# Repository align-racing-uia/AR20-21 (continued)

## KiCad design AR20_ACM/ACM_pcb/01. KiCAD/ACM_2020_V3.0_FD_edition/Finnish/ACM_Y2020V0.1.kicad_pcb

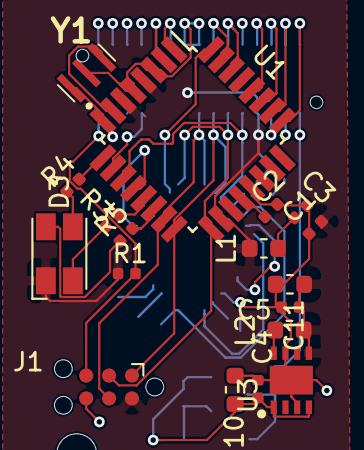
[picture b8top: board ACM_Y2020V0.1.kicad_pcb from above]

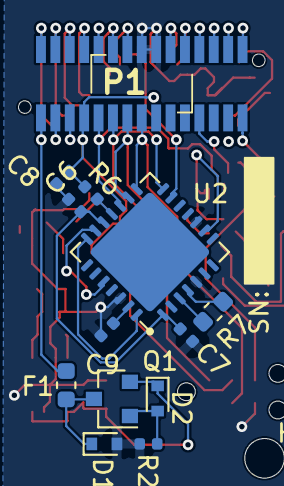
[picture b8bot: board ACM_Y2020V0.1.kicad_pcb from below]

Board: 2 copper layers, 32 parts (14 on the bottom side), 40 nets.

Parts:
C1, C2, C3, C4, C5, C6, C7, C8, C9: 0.1uF; C_0402_1005Metric
C10, C11: 10uF; C_0603_1608Metric
D1: 15V; D_SOD-523
D2: 2.4V; D_SOD-523
D3: ASMB-MTB0-0A3A2; LED_Avago_PLCC4_3.2x2.8mm_CW
F1: 250mA; Fuse_0603_1608Metric
H1: M2 Mouting hole; MountingHole_2.2mm_M2
J1: TC2030-MCP-NL; Tag-Connect_TC2030-IDC-NL_2x03_P1.27mm_Vertical
L1: 10uH; L_0603_1608Metric
L2: 2.2 µH; L_0603_1608Metric
P1: Conn_02x15_Odd_Even; ILWX10SBVFBE
Q1: Q_PMOS_DGS; SOT-23
R1, R6: 10K Ohm; R_0402_1005Metric
R2: 100K Ohm; R_0402_1005Metric
R3: 290 ohm; R_0402_1005Metric
R4: 200ohm; R_0402_1005Metric
R5: 190 Ohm; R_0402_1005Metric
R7: 120 Ohm; R_0603_1608Metric
U1: ATmega328P-AU; TQFP-32_7x7mm_P0.8mm
U2: MCP25625-x-SS; QFN-28-1EP_6x6mm_P0.65mm_EP4.8x4.8mm
U3: NCV890430MW50TXG; SON65P300X300X100-9N
Y1: 16.0Mhz; CSTNE16M0V530000R0

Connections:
+5V: C1.1, C5.1, C6.1, C11.1, D3.1, J1.2, L1.1, L2.2, P1.7, R1.1, R6.2, U1.4, U1.6, U1.18, U3.5
+12V: F1.2, P1.1
+12V_Safe: C4.1, C10.1, D2.1, Q1.2, U3.1, U3.4
/BLUE_LED: R5.2, U1.14
/CAN_CS: P1.9, U1.11, U2.17
/CAN_INT: U1.32, U2.13
/CLK_MCP: U1.12, U2.9
/GREEN_LED: R4.2, U1.9
/MISO: J1.1, P1.13, U1.16, U2.16
/MOSI: J1.4, P1.15, U1.15, U2.15
/RED_LED: R3.2, U1.13
/Reset: J1.5, P1.29, R1.2
/SCK: J1.3, P1.11, U1.17, U2.14
/U-Pin1: R7.2, U2.3
/U-Pin2: P1.2, U1.25
/U-Pin3: R7.1, U2.4
/U-Pin4: P1.4, U1.26
/U-Pin6: P1.6, U1.27
/U-Pin8: P1.8, U1.28
/U-Pin12: P1.12, U1.30
/U-Pin14: P1.14, U1.31
/U-Pin20: P1.20, U1.1
/U-Pin22: P1.22, U1.2
/U-Pin23: P1.23, U1.10
GND: C1.2, C2.2, C3.1, C4.2, C5.2, C6.2, C7.2, C8.2, C9.1, C10.2, C11.2, D1.2, J1.6, P1.16, P1.18, R2.2, U1.3, U1.5, U1.21, U2.5, U2.10, U2.26, U3.3, U3.7, U3.9, Y1.2
unnamed: C2.1, U1.20
unnamed: C3.2, L1.2
unnamed: C7.1, C8.1, U2.1, U2.19
unnamed: C9.2, U2.27
unnamed: D1.1, F1.1, Q1.3
unnamed: D2.2, Q1.1, R2.1
unnamed: D3.2, R5.1
unnamed: D3.3, R4.1
unnamed: D3.4, R3.1
unnamed: L2.1, U3.8
unnamed: R6.1, U2.18
unnamed: U1.7, Y1.3
unnamed: U1.8, Y1.1
unnamed: U2.20, U2.24
unnamed: U2.21, U2.28

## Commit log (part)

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2019-11-11 Fixed test points
2019-11-11 MCP25625 Breakoutboard Ready
2019-11-11 Added Gerberfiles
2019-11-13 CPU canEvents
2019-11-13 Breakout Cpu
    WIP
2019-11-14 Breakout CPU FIX
    fixed can
2019-11-14 Breakout CPU no connections added
2019-11-14 Breakout CPU with SD card
2019-11-14 CPU RTOS Msgs added
    Can send strings between threads
2019-11-18 Uart brakeout board
2019-11-20 Auto stash amerge of "master" and "origin/master"
2019-11-20 CPU Stash
2019-11-20 Flyttet på komponent
2019-11-20 Auto stash before merge of "master" and "origin/master"
2019-11-20 mohammad_edition
2019-11-20 Created Simon Edition Folder
2019-11-20 AtmegaFix
2019-11-20 Exploded and connected MCP25625 RX and TX
2019-11-20 Exploded and connected MCP25625 RX and TX 2
2019-11-20 Edited schematic breakout teensy
2019-11-20 Added right ICSP connector pinout
2019-11-20 Revert "Merge branch 'master' into GPS"
    This reverts commit eede9093351da36afd50b96e1e304890f671bac6.
2019-11-22 Added footprint to connectors
2019-11-22 Edited test points
2019-11-22 ADDED NEW FOOTPRINT TO TEENSY CONNECTORS
2019-11-22 FOOTPRINT IS DONE
2019-11-24 Added some trace to PCB
2019-11-24 initial traces is done
2019-11-24 Made a copy of Teensy schematic
2019-11-27 Edited library
2019-11-29 Edited the layout
2019-12-04 Edited to 4 layers
2019-12-06 4 Layers PCB is 90% finished
2019-12-09 BreakoutBoard final edit
2019-12-10 Edited the Vreg to SD
2019-12-18 Edited
2020-01-07 Created Steering Angle sensor PCB
2020-01-07 Added: 90deg JST XH connector
2020-01-07 Added Renders
2020-01-07 Changed size due to 10x10mm potmeter
2020-01-07 Updated Render
2020-01-11 Added: M. Edition
2020-01-12 ready pcb ACM
2020-01-12 ACM Folder Cleanup
2020-01-12 Fixed push button
2020-01-12 ACM-pcb full connected
    ACM -12.01
2020-01-12 final one 12.01
2020-01-12 Ronded corner and added a angle
2020-01-12 Set PCB Size and started on ACM footprint
2020-01-12 Added GND to Pin 9 and checked connector output
2020-01-12 Created ACM2020 Footprint (.kicad_mod) and Symbol (.lib)
2020-01-13 Created ACM Breakout
2020-01-13 Pad to close to pad issue
2020-01-13 Pad to close to pad
2020-01-13 Generated Gerber
2020-01-13 GerberFile Generated
2020-01-13 Generated Breakout Gerber
2020-01-13 Generated ACM Gerber
2020-01-14 Gerber
2020-01-15 Added Telemetry Extention folder
2020-01-15 Added ACM Library: See Git description
    Added ACM footprint
    Added ACM Symbol
2020-01-17 Intitialized ACM Pedalbox
2020-01-17 Created PlatformIO Project
2020-01-17 Created converted emulator
2020-01-18 Checkout
2020-01-18 Checkout ()
2020-01-18 Added symbols
2020-01-19 Git ignore
2020-01-20 Created ETBC Ramp function
2020-01-20 Testet ETBC with ramp functions and oscilloscope.
2020-01-20 Added math in Waveforms
2020-01-21 NEW Gerber File generated
2020-01-21 Gerber.zip
2020-01-22 Added data from the car
2020-01-22 Added lots of stuff
2020-01-22 Closed waveforms
2020-01-22 Added ACM2020 Footprint
2020-01-22 Initialized: Pedalbox Extention board
2020-01-22 See Changelog
    Added: ACM Library
    Added: 2x Voltage dividers
    Added: Connector
2020-01-23 Started on PCB layout and added 18pin connector
2020-01-23 Initialized new ETBC controller
2020-01-23 Added libraries
2020-01-23 Ignore me
2020-01-23 Started on schematic
2020-01-24 Added new test data on bench for 40mm ETB.
2020-01-24 Matlab Fourier Transform Script
2020-01-27 Finnish Matlab Fourier script (See Description)
    Unsure if the X-axis is right.
2020-01-27 Shematic
    Added leds
    Added small components
2020-01-28 Connector change
2020-01-29 Pedalbox PCB Ready - Just need some more silkscreen... ;)
2020-01-30 Edit pads
2020-01-30 Edit pads and traces
2020-01-30 Fixed traces, changed ACM footprint and generated gerber
2020-01-30 Gerber file 1.0 generated
2020-01-30 Generated gerber for breakout board
2020-01-30 Generated Gerber Zip
2020-01-30 Added Endurance race
2020-01-31 Created LPF calc
2020-01-31 Added Resistor and capacitor to calc
2020-01-31 Created PCB BOM
2020-02-01 Low pass filter calc
2020-02-02 Added connector
2020-02-02 Added ACM Connector
2020-02-02 Added filters
2020-02-03 Added controller datasheet
2020-02-03 Se Changelog in description
    Changed connector
    Added Capacitors
    Set footprints
2020-02-04 Datasheet save
2020-02-04 Uknown
2020-02-07 Frequency test
2020-02-09 Voltage_Regulator added
2020-02-09 Added MCP25625 symbol
2020-02-09 Made v0.1
2020-02-10 ecuCode
2020-02-10 Connector footprint added
2020-02-10 Connector added
2020-02-11 Fourier Transform fix
2020-02-11 DataLoggerAR20
2020-02-12 Created 3D Step of Pedal MCU
2020-02-12 Frequency test (10Hz - 50Hz, 10Hz intervall)
2020-02-12 Size of PCB
2020-02-17 ETBC code
2020-02-17 Created functions.h
2020-02-17 code V1.1 testing
2020-02-18 Added different types of waveforms functions
2020-02-20 Generated EGS folder
2020-02-26 Code V1.2
2020-02-29 Alot of polishing, and bug fixes, se description.
    - Fixed wrong header names in CSV
    - Reduced decimal precision
    - Added a SD_operations file, where all SD operations occur
    - Changed data rate to 100ms
    - Added F macro to texts, to reduce ram usage. Program failed due high ram usage.
    - Added temperature sensor bound's.
2020-03-02 Created BOM
2020-03-02 Prototype board extention
2020-03-03 Value change
2020-03-03 Changed footprint
2020-03-03 ETC PCB Layout
2020-03-04 Added correct MCP25625 symbol - Need to be converted in schematic
2020-03-04 Adjusted footprints and created BOM
2020-03-04 ACM_V2.0 edition: Ny pcb design
    fixet MCP footprint
2020-03-05 ETBC Semi complete - Evryting connected. Check description
    Neec to check all footprints.
    Need to check all symbols (Pin numbering correspond to footprint and datasheet)
    Need to check JLCPCB DRC settings.
2020-03-06 ETBC Complete
2020-03-07 Simon adjustment 1 of 2
2020-03-07 Checked MCP25625 and adjusted traces.
2020-03-07 V2.0 Teensy Breakout Board
2020-03-07 Push button edited
2020-03-08 Edited traces
2020-03-09 Added Datasheets
2020-03-12 Created 3D Model
2020-03-22 Settings adjustment
2020-03-25 Endret SCLK pin til SD
2020-03-30 code settings
2020-03-31 More PWM Datapoints
2020-04-29 Generated Renders for V1.1
2020-05-11 Generated 3D Model
2020-05-11 Added: 3D Component ACM connector
2020-05-16 Added: Data from Solan test
2020-05-22 Generated 3D file
2020-09-10 Deleted everything except ACM folder in ACM-branch
    Test
2020-09-15 Cleaned the inventory, Added moccup Code
2020-09-19 Cleanup
2020-09-19 test
2020-09-19 Del test
2020-09-19 Added: "Reformatting code" (Work from AR20)
2020-09-19 Cleanup
    Only AR20_Pedalbox folder in this branch.
2020-09-19 Cleanup
    Only "AR20_steeringAngle" folder in this branch
2020-09-19 Cleanup
    Only "AR20_ETC" folder in this branch.
2020-09-20 Major Cleanup Action
2020-09-20 Major Cleanup, Own Branch For RTOS
2020-09-22 Added ACM Cad in 3d View
2020-09-22 Moved library folder /lib
2020-09-23 created test.txt
2020-09-24 Fixed system in 2layer folder, probably need some more work
2020-09-27 Circuit protecion fixed
2020-09-27 Changed RGB light
2020-09-28 Minor Library fix
2020-10-01 NOT COMPLETE V3.0 ACM
    This is the beginning of the V3.0 ACM. With added CAN FD transiver and CAN FD controller.
    To fix:
    Chagne CAN FD transciver to a SOCI version
    Place all capacitors in a good location.
    Board cleanup
2020-10-03 ACM 3.0 CAN FD implemented and made SOIC
2020-10-06 Better connections
    Gave groundplane a better route and moved some 5V
2020-10-11 Added: 2x Connectors and 2x pads.
2020-10-13 Added Zener diode between 5V and ground
2020-10-18 20Mhz resonator on CAN Conrtoller
2020-10-20 High Termal Design of ETBC, on the works
    Almost done, finishing left
2020-10-21 Changed footprint for connector
2020-10-22 Work in progress
2020-10-22 Moved mosfet out of 12V safe
    Moved the mosfet outside of the safe filtered 12V. Still placed behind the fuse, so nothing interferes before the fuse does it's job.
2020-10-24 V2.3 Better design Done
    -New PCB
    -Got rid of superfluous Diode
    -Got rid of poor choise Resistors in low pass filter
2020-10-24 Some 3D Work
2020-11-02 Added namings to the ports
2020-11-07 Started creation of RS485 board
2020-11-09 Reverse polarity protection
2020-11-11 Start of V3 STM32
    Imported symbols/footprints ...
2020-11-12 Silkscreen update
2020-12-05 slight schematics cleanup
2020-12-09 Changed Zener Diode from 3.6V to 5.1V
2020-12-13 Added connector footprint to KiCad
2020-12-13 Added Protection circuit as in CAN FD ACM
2020-12-13 Deletet redundant stuff
    - deleted breakout boards, they are in the ACM brach
2020-12-13 Generated Gerber FIles
2020-12-13 Cleanup of old ACM 2.0 files And generated Gerber
    - Deleted ACM 2 First Edition. it is in ACM2.0 branch
    - Deletetd ACM 2 CAN2.0 related folders it is in ACM2.0 branch
    - Deleted Eale Project as it exist in ACM 2.0 Branch
2020-12-13 Battery PCB completed
2020-12-13 Fixed: Mounting holes
2020-12-13 Added awesome, and Generated ZiP
2020-12-13 Added awesome, and Generated Gerber
2020-12-13 Updated Silk_scr and Generated Gerber
2020-12-13 Fixed a little issue, New gerber files
2020-12-16 Footprint and schematics H7
2020-12-16 Test2
2020-12-17 Imported FDCAN Chip
2020-12-17 Added FCCAN ship from standard lib
    Regner med at denne er riktig? Har ikke sjekket om det er riktig pakning eller mål, men dette er litt forvirrende. Får ta dette med Christian
2020-12-17 Suspension disp senson schematic done
2020-12-19 Added footprints diodes ++
2020-12-30 Nearly completed schematics. Ready for tracing?
    Short cleanup in footprint library
2021-01-05 PCB trace 1.0V
    Har ikke lagt til spenningsforsyning til sensorene eller GND. Dessuten har jeg satt connectoren feil vei
2021-01-06 Schematic DONE, started tracing
2021-01-10 Trace V1.0 take 1
2021-01-10 Small fixes. Not done yet
2021-01-11 A slight Adjustment
2021-01-11 Re save
2021-01-17 Generated gerbers
2021-02-13 Created iBOM
2021-02-13 Set filtering values
2021-02-13 Updated iBOM
2021-03-03 Moved Gerber to folder and zipped it.
2021-03-13 Beginnings Gear Sensor
    The simple beginnings of a project that might revolutionize the world
2021-03-15 Added 10k resistor between VDD and CS
    As requested by the ACAN library I added a 10k resistor between VDD and CS
2021-03-15 Some demo code for gear sensor and clutch pressure
2021-03-18 Updated 10k resistor position and version
2021-03-20 V3 EGS code library based
2021-03-20 Comment
2021-03-24 Lagt til kode for testing av CANbus
2021-03-27 CANbus endringer
2021-04-07 Bug fix attempt
2021-04-07 Fungerende platformoi.ini fil som flasher kode
2021-04-11 CANbus, fungerer nesten
2021-04-11 Beginning working code for clutch servo
2021-04-12 Moved code to object oriented
2021-04-14 Dysfunctional code
2021-04-14 Compiling code
2021-04-14 Fungerer greit nok
2021-04-18 it's alive(ish)
    koden er ikke laget, men det kompilerer
2021-04-19 Startet på logikk
    Naboen går med boblejakke og spiser is
2021-04-20 Lagd mockup
    grov
2021-04-21 Mockup Code
2021-04-22 Code managed by main.cpp
2021-04-23 Code environment cleanup
2021-04-23 Hope this works
    vil ha is
2021-04-23 Commiting from VSCode
2021-04-23 Unfinnished merge between EGS and EGS logic
2021-04-23 Merge branch 'EGS_main_logic' functioning merge with logic
    Conflicts:
    AR20_EGS/EGS code V3/.pio/build/project.checksum
    AR20_EGS/EGS code V3/.vscode/c_cpp_properties.json
    AR20_EGS/EGS code V3/.vscode/extensions.json
    AR20_EGS/EGS code V3/.vscode/launch.json
    AR20_EGS/EGS code V3/platformio.ini
2021-04-24 Added commands to logic
2021-04-25 Changed the genneral flow of the program
    Made a pinout table for easy referance to what the ports do.
    Changed the program to a less blocking code structure.
    Removed most of the printing since it caused memory problems.
2021-04-26 Added ability to go to neutral if in 1 and out if in neutral
2021-04-27 Added commands through serial, minor bug fixes and removed some unused variables
2021-05-06 Error messages over CAN
2021-05-15 Can Recieve
2021-05-26 Removed debug code, added some more error handeling. And more
2021-06-19 Pinout change
2021-06-29 Starting Sensor Read project
2021-06-30 Work
2021-07-02 New project
2021-07-05 Interrupt code
2021-07-06 AnalogRead code
